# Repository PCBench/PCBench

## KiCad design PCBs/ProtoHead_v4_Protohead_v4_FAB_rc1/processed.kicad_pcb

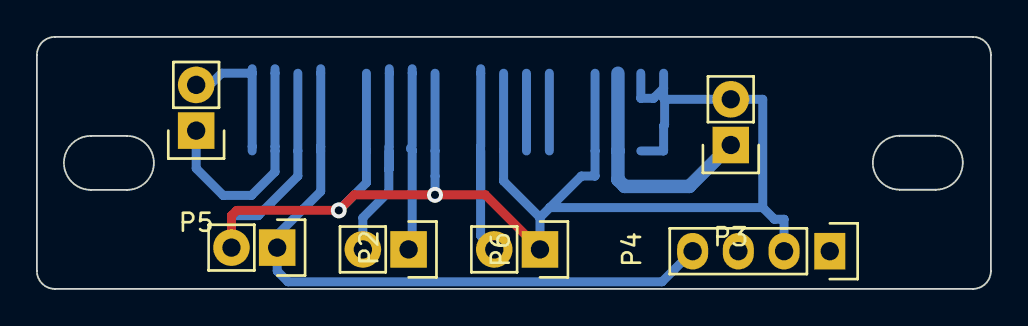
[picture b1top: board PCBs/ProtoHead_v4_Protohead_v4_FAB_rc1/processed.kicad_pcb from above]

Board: 2 copper layers, 53.0 x 14.0 mm, 7 parts (1 on the bottom side), 8 nets.

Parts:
P1: FABTOTUM_HEAD_NOMOTOR_CONNECTOR; IntegratedBourns_nomotor_smd
P2: FAN; Pin_Header_Straight_1x02
P3: HEATER; Pin_Header_Straight_1x02
P4: BLOWER; Pin_Header_Straight_1x02
P5: THERMISTOR; Pin_Header_Straight_1x02
P6: I2C; Pin_Header_Straight_1x02
P7: Arduino_Mini_RAW_GND_RST_VCC; Socket_Strip_Straight_1x04

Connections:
GND: P1.1, P1.2, P1.4, P1.7, P1.9, P1.12, P1.14, P2.2, P3.2, P4.1, P7.2
unnamed: P1.3, P3.1
unnamed: P1.8, P4.2
unnamed: P1.10, P6.1
unnamed: P1.11, P6.2
unnamed: P1.13, P2.1, P7.4
unnamed: P1.15, P5.1
unnamed: P1.16, P5.2

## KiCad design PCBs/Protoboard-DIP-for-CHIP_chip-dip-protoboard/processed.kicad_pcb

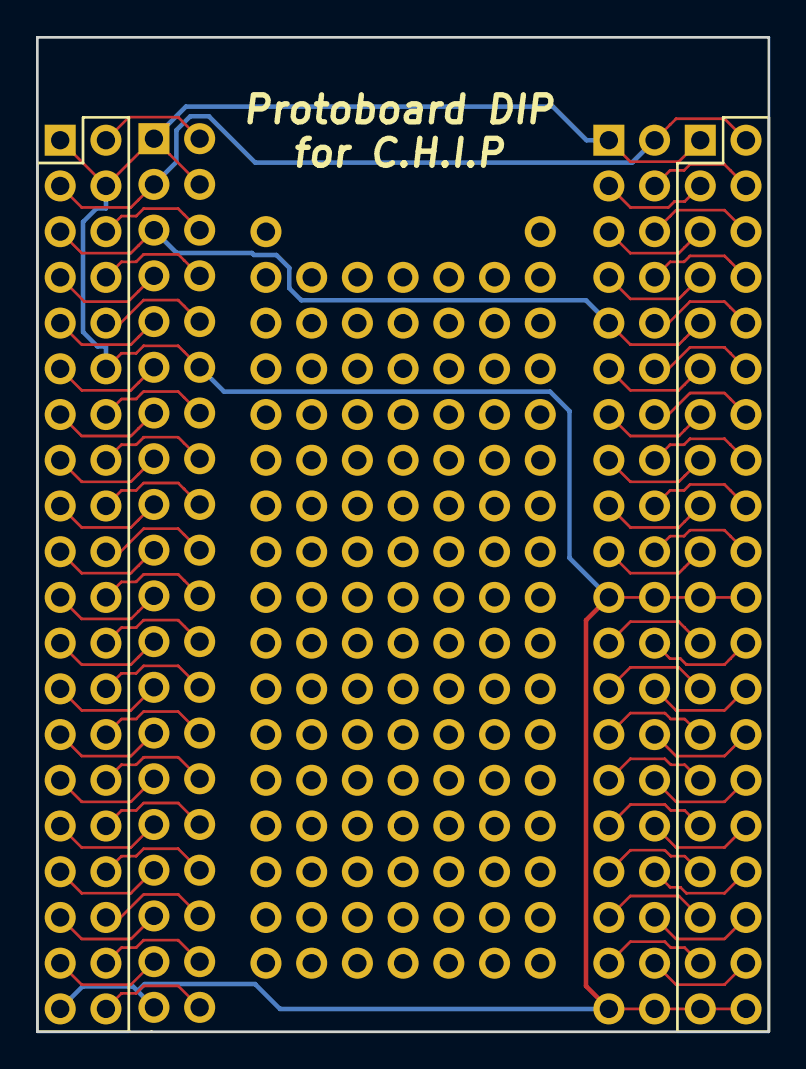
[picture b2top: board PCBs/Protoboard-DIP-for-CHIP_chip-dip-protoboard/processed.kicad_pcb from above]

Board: 2 copper layers, 40.6 x 55.2 mm, 120 parts (0 on the bottom side), 70 nets.

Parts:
DNP1, DNP2, DNP3, DNP4: HOLES; Protoboard_Holes_1x20
J13, J14: DIP-HEADER-2x20; DIP_Header_2x20
V33, V34, V35, V36, V37, V38, V39, V44, V45, V46, V47, V48, V49, V54, V55, V56, V57, V58, V59, V64, V64_2, V65, V65_2, V66, V66_2, V67, V67_2, V68, V68_2, V69, V69_2, V74, V75, V76, V77, V78, V79, V83, V84, V85, V86, V87, V88, V89, V310, V311, V312, V313, V314, V315, V316, V317, V318, V319, V410, V411, V412, V413, V414, V415, V416, V417, V418, V419, V510, V511, V512, V513, V514, V515, V516, V517, V518, V519, V610, V610_2, V611, V611_2, V612, V612_2, V613, V613_2, V614, V614_2, V615, V615_2, V616, V616_2, V617, V617_2, V618, V618_2, V619, V619_2, V710, V711, V712, V713, V714, V715, V716, V717, V718, V719, V810, V811, V812, V813, V814, V815, V816, V817, V818, V819: PINHOLE-40MIL

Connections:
+1.8V: DNP1.4, J13.7
+3.3V: DNP1.3, DNP3.5, J13.5, J14.9
+5V: DNP1.2, DNP4.1, J13.3, J14.2
/AP-EINT1: DNP3.12, J14.23
/AP-EINT3: DNP4.12, J14.24
/CSICK: DNP4.14, J14.28
/CSID0: DNP3.16, J14.31
/CSID1: DNP4.16, J14.32
/CSID2: DNP3.17, J14.33
/CSID3: DNP4.17, J14.34
/CSID4: DNP3.18, J14.35
/CSID5: DNP4.18, J14.36
/CSID6: DNP3.19, J14.37
/CSID7: DNP4.19, J14.38
/CSIHSYNC: DNP3.15, J14.29
/CSIPCK: DNP3.14, J14.27
/CSIVSYNC: DNP4.15, J14.30
/FEL: DNP3.4, J14.7
/HPCOM: DNP4.3, J14.6
/HPL: DNP4.2, J14.4
/HPR: DNP4.4, J14.8
/LCD-CLK: DNP1.18, J13.35
/LCD-D2: DNP1.9, J13.17
/LCD-D3: DNP2.10, J13.20
/LCD-D4: DNP1.10, J13.19
/LCD-D5: DNP2.11, J13.22
/LCD-D6: DNP1.11, J13.21
/LCD-D7: DNP2.12, J13.24
/LCD-D10: DNP1.12, J13.23
/LCD-D11: DNP2.13, J13.26
/LCD-D12: DNP1.13, J13.25
/LCD-D13: DNP2.14, J13.28
/LCD-D14: DNP1.14, J13.27
/LCD-D15: DNP2.15, J13.30
/LCD-D18: DNP1.15, J13.29
/LCD-D19: DNP2.16, J13.32
/LCD-D20: DNP1.16, J13.31
/LCD-D21: DNP2.17, J13.34
/LCD-D22: DNP1.17, J13.33
/LCD-D23: DNP2.18, J13.36
/LCD-DE: DNP2.20, J13.40
/LCD-HSYNC: DNP2.19, J13.38
/LCD-VSYNC: DNP1.19, J13.37
/LRADC: DNP3.6, J14.11
/MICIN1: DNP4.6, J14.12
/MICM: DNP4.5, J14.10
/PWM0: DNP2.9, J13.18
/PWRON: DNP2.5, J13.10
/TS: DNP2.3, J13.6
/TWI1-SCK: DNP1.6, J13.11
/TWI1-SDA: DNP1.5, J13.9
/TWI2-SCK: DNP4.13, J14.26
/TWI2-SDA: DNP3.13, J14.25
/UART1-RX: DNP3.3, J14.5
/UART1-TX: DNP3.2, J14.3
/X1: DNP1.7, J13.13
/X2: DNP2.7, J13.14
/XIO-P0: DNP3.7, J14.13
/XIO-P1: DNP4.7, J14.14
/XIO-P2: DNP3.8, J14.15
/XIO-P3: DNP4.8, J14.16
/XIO-P4: DNP3.9, J14.17
/XIO-P5: DNP4.9, J14.18
/XIO-P6: DNP3.10, J14.19
/XIO-P7: DNP4.10, J14.20
/Y1: DNP1.8, J13.15
/Y2: DNP2.8, J13.16
GND: DNP1.1, DNP1.20, DNP2.2, DNP2.6, DNP3.1, DNP3.11, DNP3.20, DNP4.11, DNP4.20, J13.1, J13.4, J13.12, J13.39, J14.1, J14.21, J14.22, J14.39, J14.40
VBAT: DNP2.4, J13.8
VCHG: DNP2.1, J13.2

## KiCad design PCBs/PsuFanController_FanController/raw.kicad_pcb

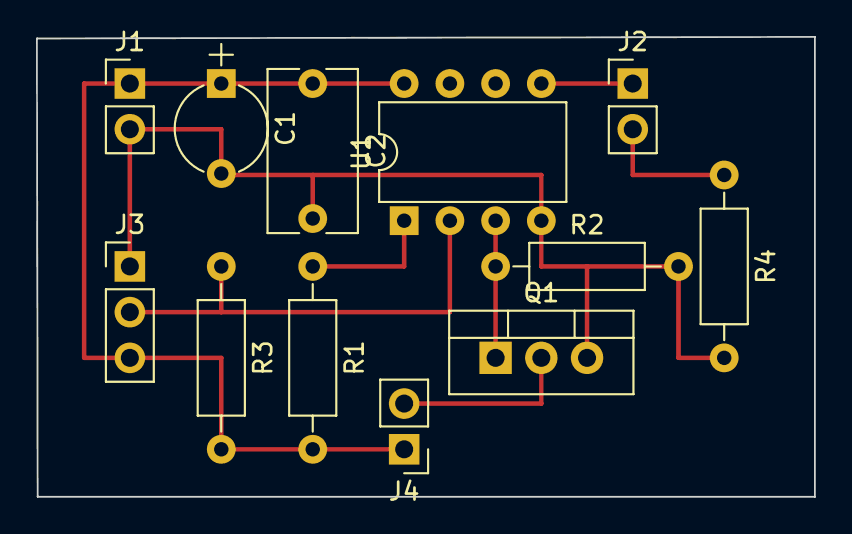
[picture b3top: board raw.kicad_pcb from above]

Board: 2 copper layers, 43.2 x 25.5 mm, 12 parts (0 on the bottom side), 8 nets.

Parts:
C1: 1uF; CP_Radial_Tantal_D5.0mm_P5.00mm
C2: 0.1uF; C_Rect_L9.0mm_W4.9mm_P7.50mm_MKT
J1: PWR; Pin_Header_Straight_1x02_Pitch2.54mm
J2: LED; Pin_Header_Straight_1x02_Pitch2.54mm
J3: DS18B20; Pin_Header_Straight_1x03_Pitch2.54mm
J4: Fan; Pin_Header_Straight_1x02_Pitch2.54mm
Q1: IRL3103PBF; TO-220_Vertical
R1, R2: 10K; R_Axial_DIN0207_L6.3mm_D2.5mm_P10.16mm_Horizontal
R3: 4K7; R_Axial_DIN0207_L6.3mm_D2.5mm_P10.16mm_Horizontal
R4: 270; R_Axial_DIN0207_L6.3mm_D2.5mm_P10.16mm_Horizontal
U1: ATTINY85-20PU; DIP-8_W7.62mm

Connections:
/VCC: C1.1, C2.1, J1.1, J3.3, J4.1, R1.2, R3.2, U1.8
GND: C1.2, C2.2, J1.2, J3.1, Q1.3, R2.2, R4.2, U1.4
unnamed: J2.1, U1.5
unnamed: J2.2, R4.1
unnamed: J3.2, R3.1, U1.2
unnamed: J4.2, Q1.2
unnamed: Q1.1, R2.1, U1.3
unnamed: R1.1, U1.1

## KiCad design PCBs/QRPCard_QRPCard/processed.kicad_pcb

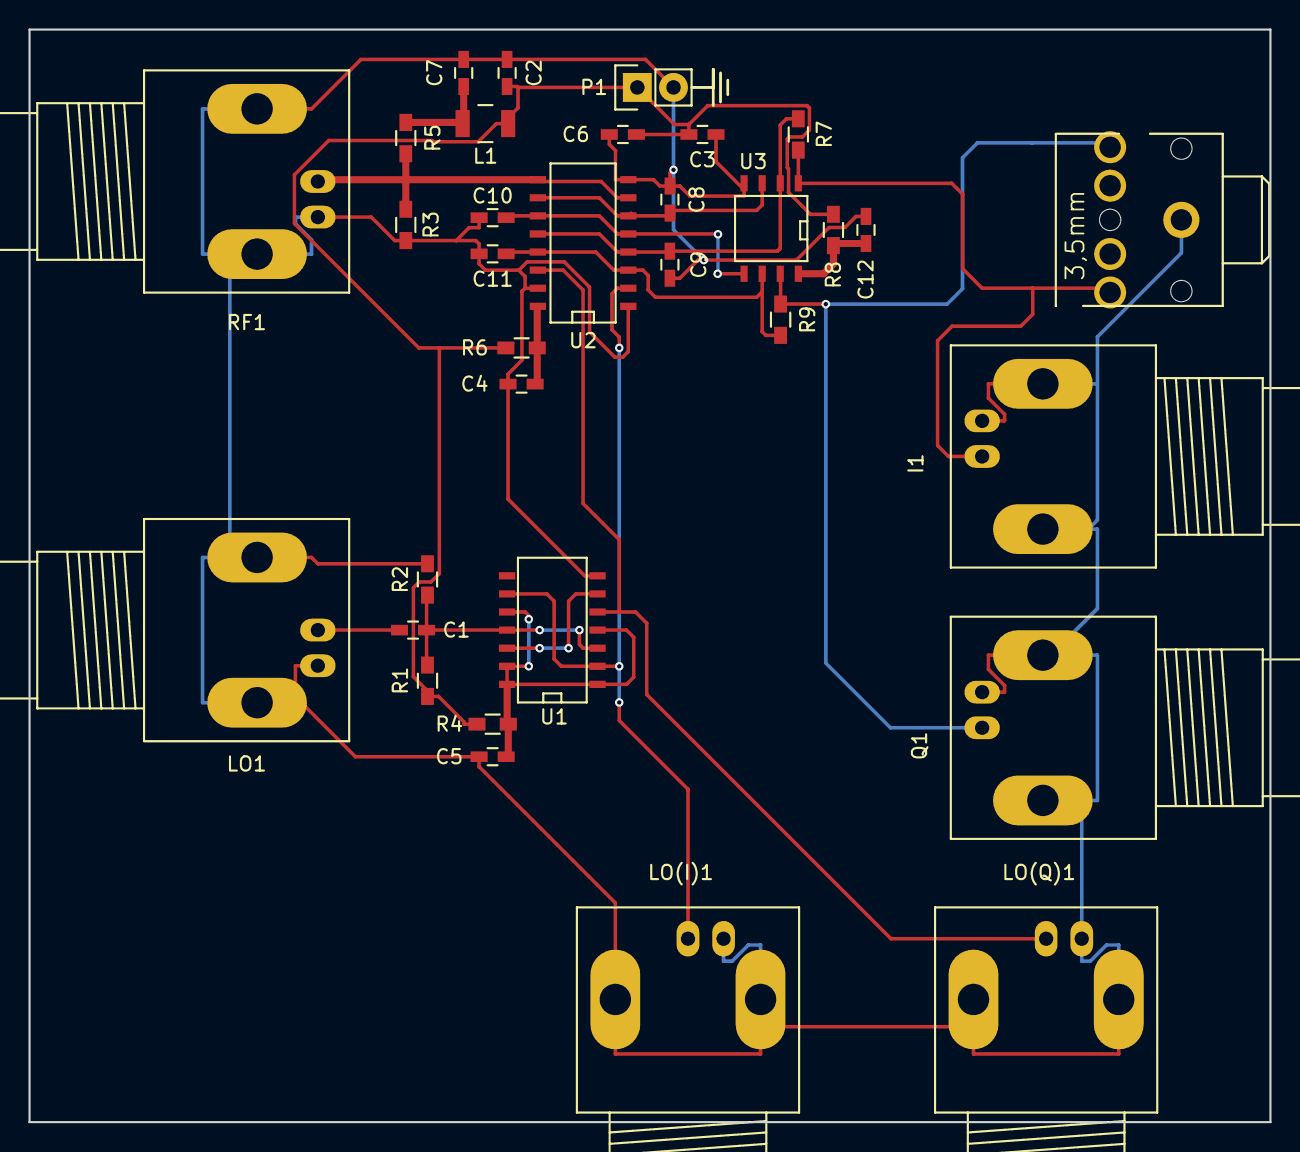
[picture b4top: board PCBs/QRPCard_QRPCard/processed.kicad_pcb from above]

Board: 2 copper layers, 87.1 x 76.7 mm, 33 parts (0 on the bottom side), 18 nets.

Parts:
C1, C4, C5, C8, C9, C10, C11, C12: 0.1uF; C_0603_HandSoldering
C2, C3, C7: 0.01uF; C_0603_HandSoldering
C6: 10uF; C_0603_HandSoldering
I1: BNC; BNC_Socket_TYCO-AMP_LargePads
J1: STX-3100-5N; STX3100
L1: 470uH; Neosid_Inductor_SM-NE30_SMD1210
LO1: BNC; BNC_Socket_TYCO-AMP_LargePads
LO(I)1: BNC; BNC_Socket_TYCO-AMP_LargePads
LO(Q)1: BNC; BNC_Socket_TYCO-AMP_LargePads
P1: +5v; Pin_Header_Straight_1x02
Q1: BNC; BNC_Socket_TYCO-AMP_LargePads
R1: 560k; R_0603_HandSoldering
R2: 220k; R_0603_HandSoldering
R3, R4, R5, R6, R8: 100; R_0603_HandSoldering
R7, R9: 100k; R_0603_HandSoldering
RF1: BNC; BNC_Socket_TYCO-AMP_LargePads
U1: SN74HC74; SOIC-14_N
U2: FST3253; SO-16-N
U3: TSV992A; SOIC-8-N

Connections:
+5V: C2.2, C3.2, C6.2, L1.1, P1.1, R1.1, R4.1, R6.1, R8.1
GND: C2.1, C3.1, C4.1, C5.2, C6.1, C7.1, C8.1, C9.1, C10.1, C11.1, C12.1, I1.2, J1.1, LO1.2, LO(I)1.2, LO(Q)1.2, P1.2, Q1.2, R2.2, R3.1, RF1.2, U1.7, U2.1, U2.8, U2.15, U3.4
unnamed: C1.1, R1.2, R2.1, U1.3, U1.11
unnamed: C1.2, LO1.1
unnamed: C4.2, R6.2, U2.16
unnamed: C5.1, R4.2, U1.1, U1.4, U1.10, U1.13, U1.14
unnamed: C7.2, L1.2, R5.1
unnamed: C8.2, U2.6, U2.10, U3.3
unnamed: C9.2, R7.2, U2.4, U2.12, U3.2
unnamed: C10.2, U2.5, U2.11, U3.5
unnamed: C11.2, R9.2, U2.3, U2.13, U3.6
unnamed: C12.2, R8.2, U3.8
unnamed: I1.1, J1.2, R7.1, U3.1
unnamed: J1.5, Q1.1, R9.1, U3.7
unnamed: LO(I)1.1, U1.2, U1.9, U2.2
unnamed: LO(Q)1.1, U1.5, U2.14
unnamed: R3.2, R5.2, RF1.1, U2.7, U2.9
unnamed: U1.6, U1.12

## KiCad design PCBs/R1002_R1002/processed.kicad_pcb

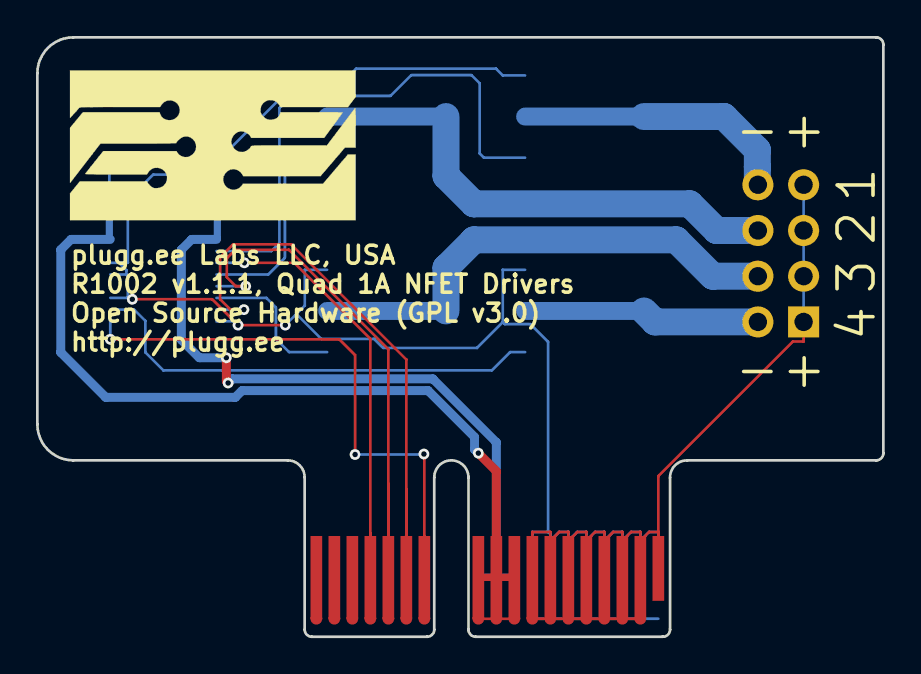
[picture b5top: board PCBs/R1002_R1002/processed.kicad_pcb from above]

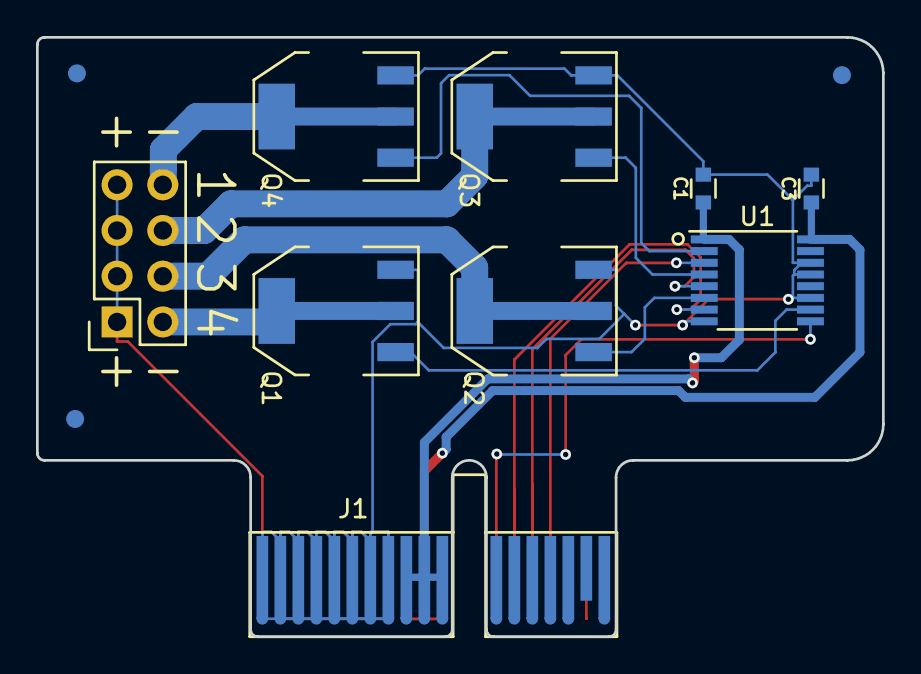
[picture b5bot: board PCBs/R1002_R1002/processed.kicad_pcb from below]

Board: 2 copper layers, 47.0 x 33.3 mm, 13 parts (12 on the bottom side), 16 nets.

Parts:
A1: ART; pluggeeLabsIcon-16X8
C1, C3: CC0603KRX7R9BB104; CAPC0603
FID1, FID2, FID3: FIDTOP001
J1: PCIEXPRESS-X1
J2: CONN254P-02X04
Q1, Q2, Q3, Q4: Q_NMOS_GDSD; SOT-223
U1: MC14504B-TSSOP; SOP65P500X440X120-16

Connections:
+3V3: C1.1, J1.B9, J1.B10, J1.B11, U1.1
+5V: C3.1, J1.A9, J1.A10, J1.A11, U1.16
/DN1: J2.8, Q4.2, Q4.4
/DN2: J2.6, Q3.2, Q3.4
/DN3: J2.4, Q2.2, Q2.4
/DN4: J2.2, Q1.2, Q1.4
/GN1: Q4.1, U1.2
/GN2: Q3.1, U1.4
/GN3: Q2.1, U1.6
/GN4: Q1.1, U1.10
GND: C1.2, C3.2, J1.B1, J1.B2, J1.B3, J1.B4, J1.B5, J1.B6, J1.B7, J1.B8, Q1.3, Q2.3, Q3.3, Q4.3, U1.8, U1.11, U1.13, U1.14
HT: J1.A1, J1.A2, J1.A3, J1.A4, J1.A5, J1.A6, J1.A7, J1.A8, J2.1, J2.3, J2.5, J2.7
PX1: J1.A12, U1.9
PX2: J1.A13, U1.7
PX3: J1.A14, U1.5
PX4: J1.A15, U1.3

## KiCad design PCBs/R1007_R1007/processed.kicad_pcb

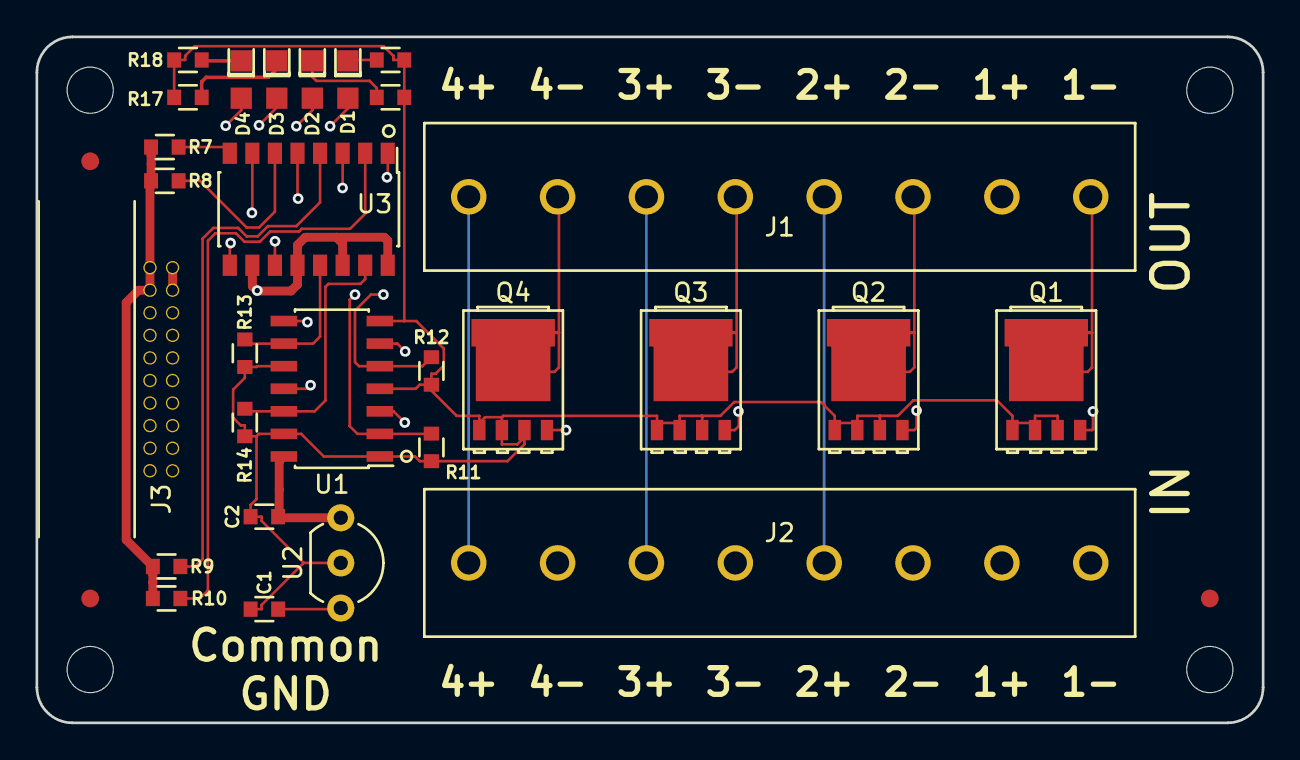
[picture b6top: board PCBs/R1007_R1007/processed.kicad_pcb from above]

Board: 4 copper layers, 69.0 x 38.6 mm, 36 parts (1 on the bottom side), 32 nets.

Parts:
A1: ART; pluggeeLabsIcon-13X7
C1, C2: CC0603KRX7R9BB104; CAPC0603
D1, D2, D3, D4: LTW-170TK; DIOC200X120X110
FID1, FID2, FID3: FIDTOP001
J1, J2: CONN500P-01X08
J3: CONN_R1000A_EXTENSION; CONN127P-02X10
MP1, MP2, MP3, MP4: MECH_NPTH_M3
Q1, Q2, Q3, Q4: PSMN1R2-30YLC; SOT127P500X110-5
R7, R8, R9, R10, R15, R16, R17, R18: RC0603FR-071KL; RESC0603
R11, R12, R13, R14: RC0603FR-074K7L; RESC0603
U1: 74HC125; SOIC127P870X390X175-14
U2: AS78L05ZTR-E1; TO92_AMMO
U3: TLP293-4; SOIC127P1030X455X210-16

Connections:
+5P: C2.1, U1.14, U2.1, U3.10, U3.12, U3.14, U3.16
/GN1: D1.2, Q1.4, U1.11
/GN2: D2.2, Q2.4, U1.8
/GN3: D3.2, Q3.4, U1.6
/GN4: D4.2, Q4.4, U1.3
/IGN1: R14.1, U1.12, U3.15
/IGN2: R13.1, U1.9, U3.13
/IGN3: R12.1, U1.5, U3.11
/IGN4: R11.1, U1.2, U3.9
/INR1: R10.1, U3.2
/INR2: R9.1, U3.4
/INR3: R8.1, U3.6
/INR4: R7.1, U3.8
/N1: J1.1, Q1.5
/N2: J1.3, Q2.5
/N3: J1.5, Q3.5
/N4: J1.7, Q4.5
/VDD2: J1.6, J2.3
/VDD3: J1.4, J2.5
/VDD4: J1.2, J2.7
GND: J3.18, J3.20, R7.2, R8.2, R9.2, R10.2
GNDPWR: C1.2, C2.2, J2.2, J2.4, J2.6, J2.8, Q1.1, Q1.2, Q1.3, Q2.1, Q2.2, Q2.3, Q3.1, Q3.2, Q3.3, Q4.1, Q4.2, Q4.3, R11.2, R12.2, R13.2, R14.2, R15.2, R16.2, R17.2, R18.2, U1.1, U1.4, U1.7, U1.10, U1.13, U2.2
HT: J3.17, J3.19
unnamed: D1.1, R15.1
unnamed: D2.1, R16.1
unnamed: D3.1, R17.1
unnamed: D4.1, R18.1
PX1: J3.13, U3.1
PX2: J3.11, U3.3
PX3: J3.9, U3.5
PX4: J3.7, U3.7
VDD: C1.1, J1.8, J2.1, U2.3

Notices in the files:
PCBs/Protoboard-DIP-for-CHIP_chip-dip-protoboard/processed.kicad_pcb:
Released under the CERN Open Hardware License v1.2
PCBs/R1002_R1002/processed.kicad_pcb:
Open Source Hardware (GPL v3.0)
